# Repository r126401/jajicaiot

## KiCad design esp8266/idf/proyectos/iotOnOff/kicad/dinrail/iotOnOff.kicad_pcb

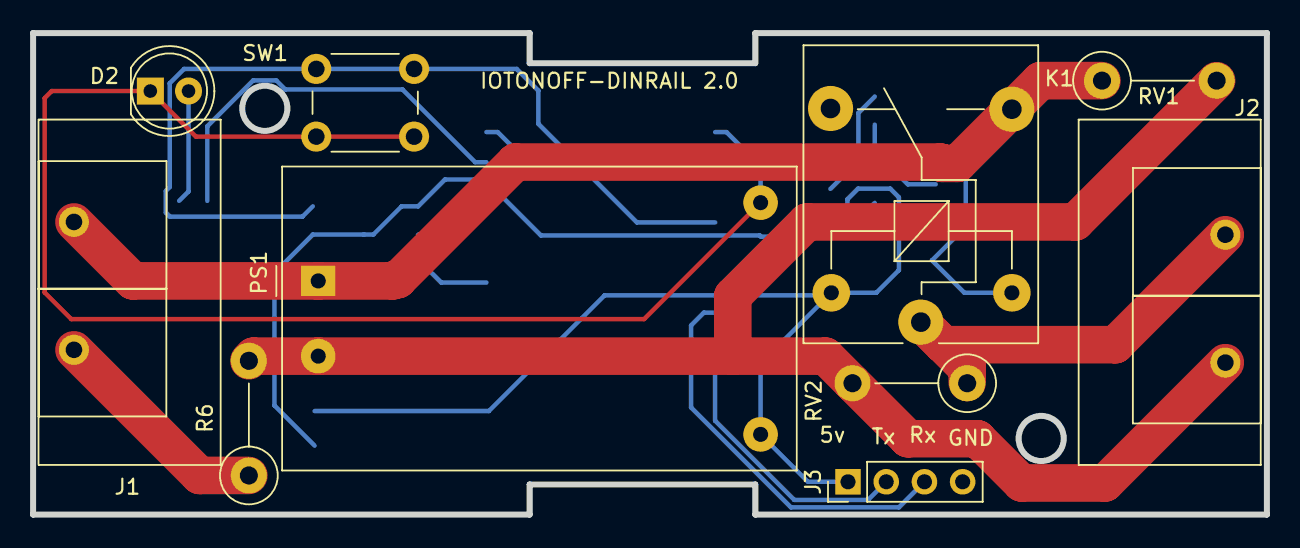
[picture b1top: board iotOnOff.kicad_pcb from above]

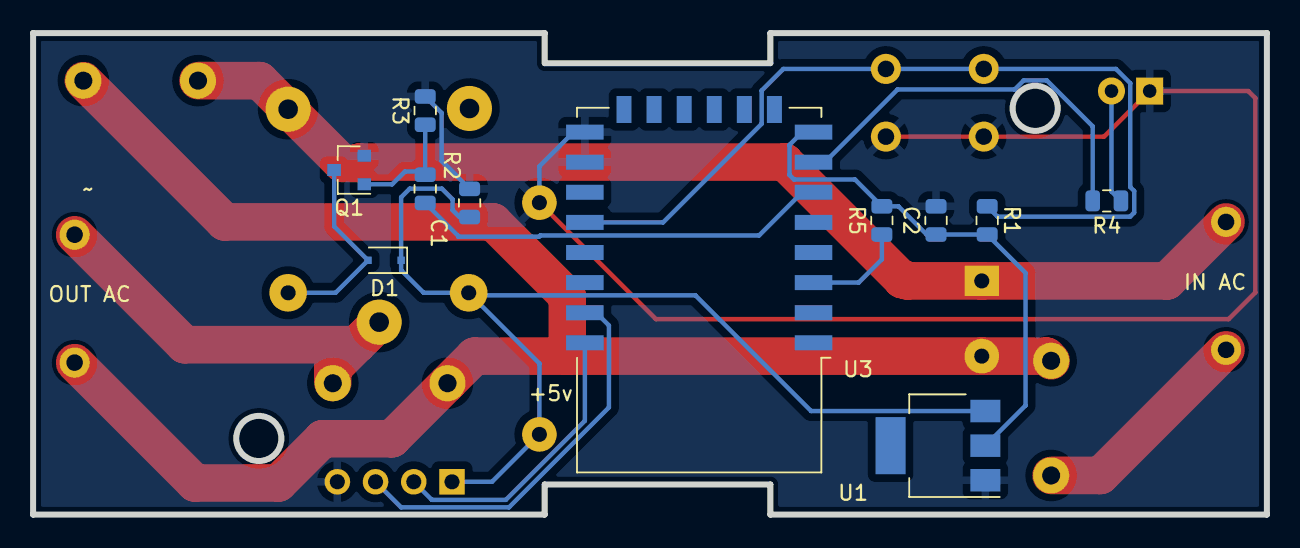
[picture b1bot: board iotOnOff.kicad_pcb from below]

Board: 2 copper layers, 82.0 x 32.0 mm, 21 parts (11 on the bottom side), 16 nets.

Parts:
C1: 10uF; C_0805_2012Metric
C2: 22uF; C_0805_2012Metric
D1: 1N4148; D_SOD-323F
D2: LED; LED_D5.0mm
J1, J2: Conn_01x02; KF8500
J3: Conn_01x04; PinHeader_1x04_P2.54mm_Vertical
K1: SANYOU_SRD_Form_A; Relay_SPDT_SANYOU_SRD_Series_Form_C
PS1: HLK-PM01; Converter_ACDC_HiLink_HLK-PMxx
Q1: 2N7002; SOT-23
R1, R3, R5: 10K; R_0805_2012Metric
R2, R4: 1K; R_0805_2012Metric
R6: 10; R_Axial_DIN0411_L9.9mm_D3.6mm_P7.62mm_Vertical
RV1, RV2: Varistor; R_Axial_DIN0411_L9.9mm_D3.6mm_P7.62mm_Vertical
SW1: SW_Push; SW_PUSH_6mm_H4.3mm
U1: AMS1117-3.3; SOT-223
U3: ESP-12F; ESP-12E

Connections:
GND: C1.2, C2.2, D2.1 (K), J3.4, PS1.3 (-Vout), Q1.2 (S), R3.2, SW1.2, U1.1 (GND), U3.15 (GND), U3.16 (GPIO15)
unnamed: C1.1, D1.1 (K), J3.1, K1.5, PS1.4 (+Vout), U1.3 (VI)
unnamed: C2.1, R1.2, R5.2, U1.2 (VO), U3.8 (VCC)
unnamed: D1.2 (A), K1.2, Q1.3 (D)
unnamed: D2.2 (A), R4.1
unnamed: J1.1, R6.1
unnamed: J1.2, K1.3, PS1.1 (AC/L), RV1.1
unnamed: J2.1, K1.1, RV2.1
unnamed: J2.2, PS1.2 (AC/N), R6.2, RV1.2, RV2.2
unnamed: J3.2, U3.22 (GPIO1/TXD)
unnamed: J3.3, U3.21 (GPIO3/RXD)
unnamed: Q1.1 (G), R2.1, R3.1
unnamed: R1.1, SW1.1, U3.18 (GPIO0)
unnamed: R2.2, U3.6 (GPIO12)
unnamed: R4.2, U3.7 (GPIO13)
unnamed: R5.1, U3.3 (EN)

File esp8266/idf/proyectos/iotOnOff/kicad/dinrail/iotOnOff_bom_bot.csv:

Comment,Designator,Footprint,LCSC Part #
2N7002,Q1,,C179727
10K,R3 R1 R5,,C17414
1K,R2 R4,,C17513
AMS1117-3.3,U1,,C347222
1N4148,D1,, C2128
10uF,C1,,C39060
22uF,C2,,C45783
ESP-12F,U3,,C82891

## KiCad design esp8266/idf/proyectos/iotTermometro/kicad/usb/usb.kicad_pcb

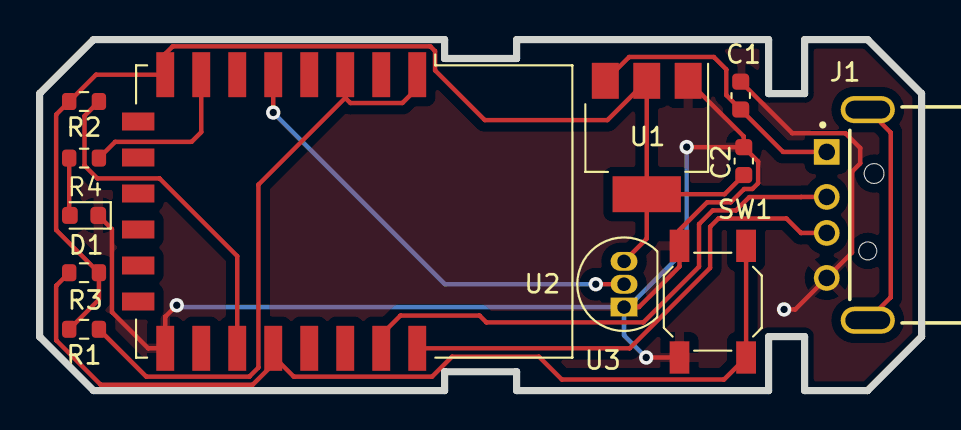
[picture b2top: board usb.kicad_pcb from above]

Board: 2 copper layers, 49.0 x 19.5 mm, 12 parts (0 on the bottom side), 11 nets.

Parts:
C1: 10u; C_0603_1608Metric
C2: 22u; C_0603_1608Metric
D1: LED; LED_0603_1608Metric
J1: USB-AM-S-X-X-TH; SAMTEC_USB-AM-S-X-X-TH
R1, R2: 10k; R_0603_1608Metric
R3, R4: 1K; R_0603_1608Metric
SW1: SW_Push; SW_SPST_SKQG_WithStem
U1: AMS1117-3.3; SOT-223-3_TabPin2
U2: ESP-12F; ESP-12E
U3: DS18B20; TO-92_Inline

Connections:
/LED_FUNCION: R4.1, U2.7 (GPIO13)
/NET_BOTON: R3.2, SW1.1, U2.18 (GPIO0)
/RX: J1.02 (D-), U2.21 (GPIO3/RXD)
/SENSOR_TEMP: U2.5 (GPIO14), U3.2 (DQ)
/TX: J1.03 (D+), U2.22 (GPIO1/TXD)
/VCC: C2.1, R1.2, R2.2, R3.1, U1.2 (VO), U2.8 (VCC), U3.3 (VDD)
/VIN: C1.1, J1.01 (VCC), U1.3 (VI)
GND: C1.2, C2.2, D1.1 (K), J1.04 (GND), SW1.2, U1.1 (GND), U2.15 (GND), U3.1 (GND)
unnamed: D1.2 (A), R4.2
unnamed: R1.1, U2.1 (~RST), U2.3 (EN)
unnamed: R2.1, U2.17 (GPIO2)

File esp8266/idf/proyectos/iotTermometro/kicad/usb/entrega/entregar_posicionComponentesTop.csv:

Ref,Val,Package,Mid X,Mid Y,Rotation,Layer
C1,10u,C_0603_1608Metric,137.950000,-72.360000,90.000000,top
C2,22u,C_0603_1608Metric,138.120000,-76.000000,90.000000,top
D1,LED,LED_0603_1608Metric,101.470000,-79.017000,180.000000,top
J1,USB_A,USB_A_CNCTech_1001-011-01101_Horizontal,150.950000,-78.998500,0.000000,top
R1,10k,R_0603_1608Metric,101.470000,-85.344000,180.000000,top
R2,10k,R_0603_1608Metric,101.470000,-72.690000,180.000000,top
R3,1K,R_0603_1608Metric,101.470000,-82.200500,180.000000,top
R4,1K,R_0603_1608Metric,101.470000,-75.833500,180.000000,top
SW1,SW_Push,SW_SPST_SKQG_WithStem,136.400000,-83.810000,-90.000000,top
U1,AMS1117,SOT-223-3_TabPin2,132.730000,-74.690000,-90.000000,top
U2,ESP-12F,ESP-12E,116.480000,-78.800000,-90.000000,top
U3,S,TO-92_Inline,131.470000,-84.110000,90.000000,top

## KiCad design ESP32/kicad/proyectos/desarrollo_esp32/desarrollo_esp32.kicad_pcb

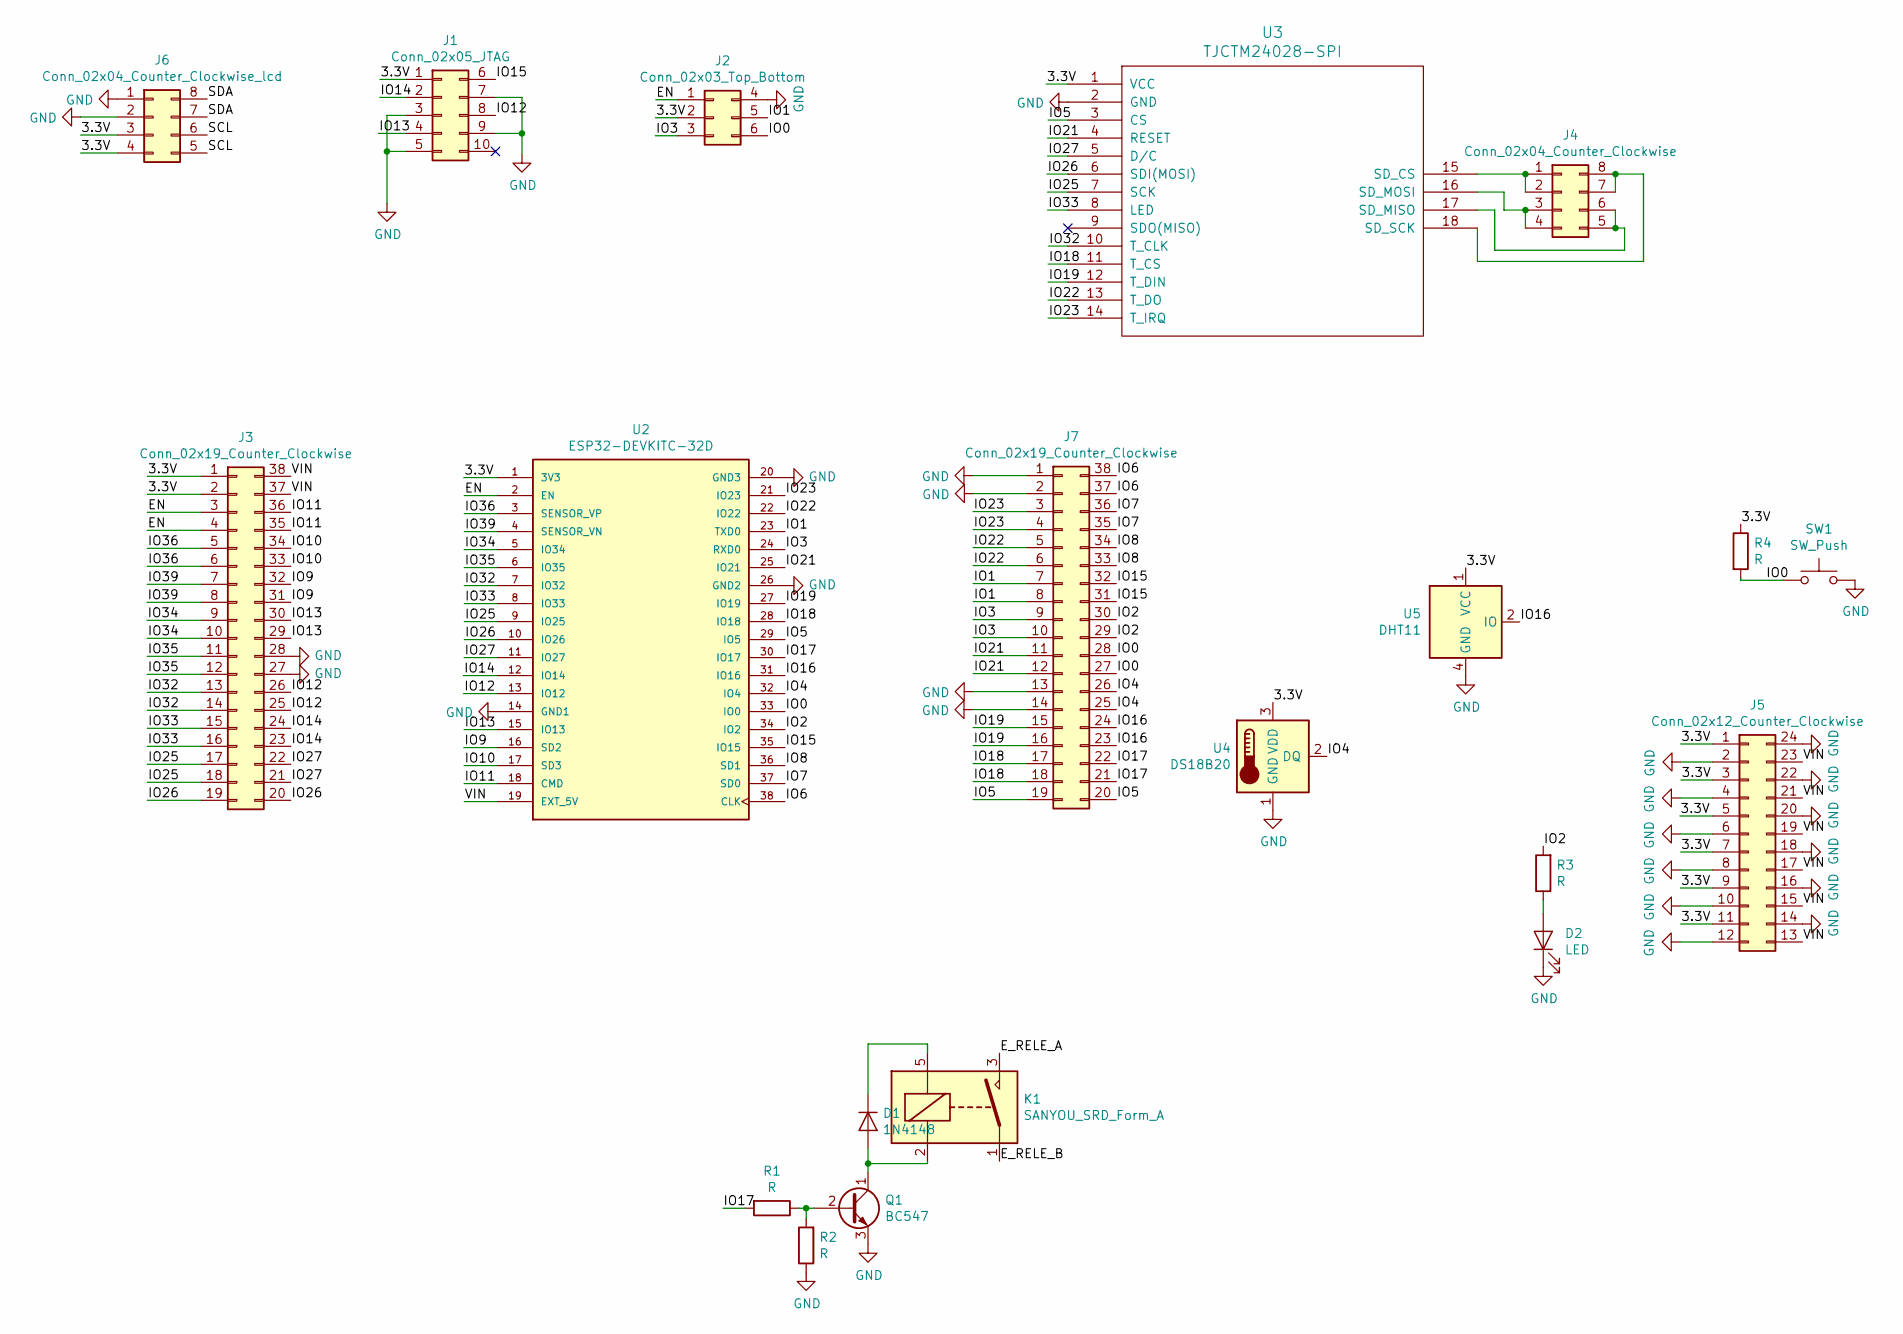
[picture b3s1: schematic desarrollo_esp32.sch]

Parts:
D1: 1N4148; D_DO-34_SOD68_P7.62mm_Horizontal
D2: LED; LED_D5.0mm
J1: Conn_02x05_JTAG; IDC-Header_2x05_P2.54mm_Vertical
J2: Conn_02x03_Top_Bottom; IDC-Header_2x03_P2.54mm_Vertical
J3, J7: Conn_02x19_Counter_Clockwise; PinSocket_2x19_P2.54mm_Vertical
J4: Conn_02x04_Counter_Clockwise; PinSocket_2x04_P2.54mm_Vertical
J5: Conn_02x12_Counter_Clockwise; PinSocket_2x12_P2.54mm_Vertical
J6: Conn_02x04_Counter_Clockwise_lcd; PinSocket_2x04_P2.54mm_Vertical
K1: SANYOU_SRD_Form_A; Relay_SPST_SANYOU_SRD_Series_Form_A
Q1: BC547; TO-92_Inline
R1, R2, R3, R4: R; R_Axial_DIN0207_L6.3mm_D2.5mm_P15.24mm_Horizontal
SW1: SW_Push; SW_PUSH_6mm_H4.3mm
U2: ESP32-DEVKITC-32D; MODULE_ESP32-DEVKITC-32D; PARTREV 4
U3: TJCTM24028-SPI; tjctm24028-spi
U4: DS18B20; TO-92_Inline
U5: DHT11; Aosong_DHT11_5.5x12.0_P2.54mm

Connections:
/3.3V: J1.1, J2.2, J3.1, J3.2, J5.1, J5.3, J5.5, J5.7, J5.9, J5.11, J6.3, J6.4, R4.1, U2.1 (3V3), U3.1 (VCC), U4.3 (VDD), U5.1 (VCC)
/EN: J2.1, J3.3, J3.4, U2.2 (EN)
/E_RELE_A: K1.3
/E_RELE_B: K1.1
/IO0: J2.6, J7.27, J7.28, R4.2, SW1.1, U2.33 (IO0)
/IO1: J2.5, J7.7, J7.8, U2.23 (TXD0)
/IO2: J7.29, J7.30, R3.2, U2.34 (IO2)
/IO3: J2.3, J7.9, J7.10, U2.24 (RXD0)
/IO4: J7.25, J7.26, U2.32 (IO4), U4.2 (DQ)
/IO5: J7.19, J7.20, U2.29 (IO5), U3.3 (CS)
/IO6: J7.37, J7.38, U2.38 (CLK)
/IO7: J7.35, J7.36, U2.37 (SD0)
/IO8: J7.33, J7.34, U2.36 (SD1)
/IO9: J3.31, J3.32, U2.16 (SD2)
/IO10: J3.33, J3.34, U2.17 (SD3)
/IO11: J3.35, J3.36, U2.18 (CMD)
/IO12: J1.8, J3.25, J3.26, U2.13 (IO12)
/IO13: J1.4, J3.29, J3.30, U2.15 (IO13)
/IO14: J1.2, J3.23, J3.24, U2.12 (IO14)
/IO15: J1.6, J7.31, J7.32, U2.35 (IO15)
/IO16: J7.23, J7.24, U2.31 (IO16), U5.2 (IO)
/IO17: J7.21, J7.22, R1.2, U2.30 (IO17)
/IO18: J7.17, J7.18, U2.28 (IO18), U3.11 (T_CS)
/IO19: J7.15, J7.16, U2.27 (IO19), U3.12 (T_DIN)
/IO21: J7.11, J7.12, U2.25 (IO21), U3.4 (RESET)
/IO22: J7.5, J7.6, U2.22 (IO22), U3.13 (T_DO)
/IO23: J7.3, J7.4, U2.21 (IO23), U3.14 (T_IRQ)
/IO25: J3.17, J3.18, U2.9 (IO25), U3.7 (SCK)
/IO26: J3.19, J3.20, U2.10 (IO26), U3.6 (SDI(MOSI))
/IO27: J3.21, J3.22, U2.11 (IO27), U3.5 (D/C)
/IO32: J3.13, J3.14, U2.7 (IO32), U3.10 (T_CLK)
/IO33: J3.15, J3.16, U2.8 (IO33), U3.8 (LED)
/IO34: J3.9, J3.10, U2.5 (IO34)
/IO35: J3.11, J3.12, U2.6 (IO35)
/IO36: J3.5, J3.6, U2.3 (SENSOR_VP)
/IO39: J3.7, J3.8, U2.4 (SENSOR_VN)
/SCL: J6.5, J6.6
/SDA: J6.7, J6.8
/VIN: J3.37, J3.38, J5.13, J5.15, J5.17, J5.19, J5.21, J5.23, U2.19 (EXT_5V)
GND: D2.1 (K), J1.3, J1.5, J1.7, J1.9, J2.4, J3.27, J3.28, J5.2, J5.4, J5.6, J5.8, J5.10, J5.12, J5.14, J5.16, J5.18, J5.20, J5.22, J5.24, J6.1, J6.2, J7.1, J7.2, J7.13, J7.14, Q1.3 (E), R2.1, SW1.2, U2.14 (GND1), U2.20 (GND3), U2.26 (GND2), U3.2 (GND), U4.1 (GND), U5.4 (GND)
unnamed: D1.1 (K), K1.5
unnamed: D1.2 (A), K1.2, Q1.1 (C)
unnamed: D2.2 (A), R3.1
unnamed: J4.1, J4.2, U3.15 (SD_CS)
unnamed: J4.3, J4.4, U3.16 (SD_MOSI)
unnamed: J4.5, J4.6, U3.17 (SD_MISO)
unnamed: J4.7, J4.8, U3.18 (SD_SCK)
unnamed: Q1.2 (B), R1.1, R2.2

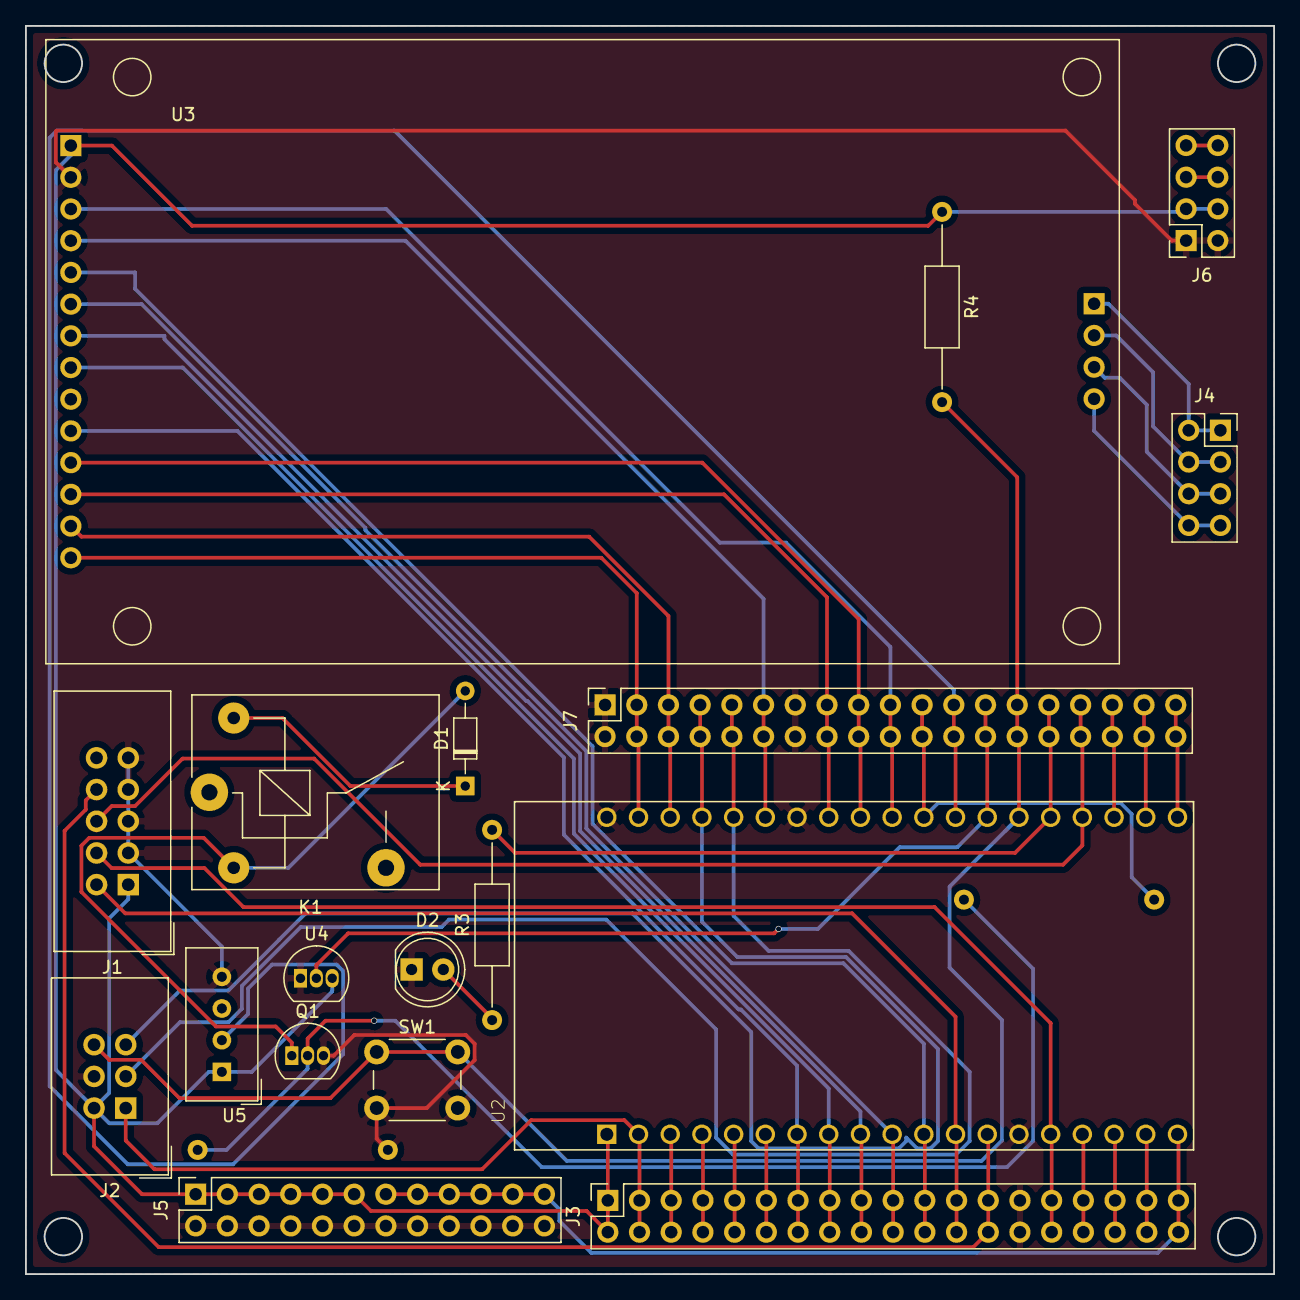
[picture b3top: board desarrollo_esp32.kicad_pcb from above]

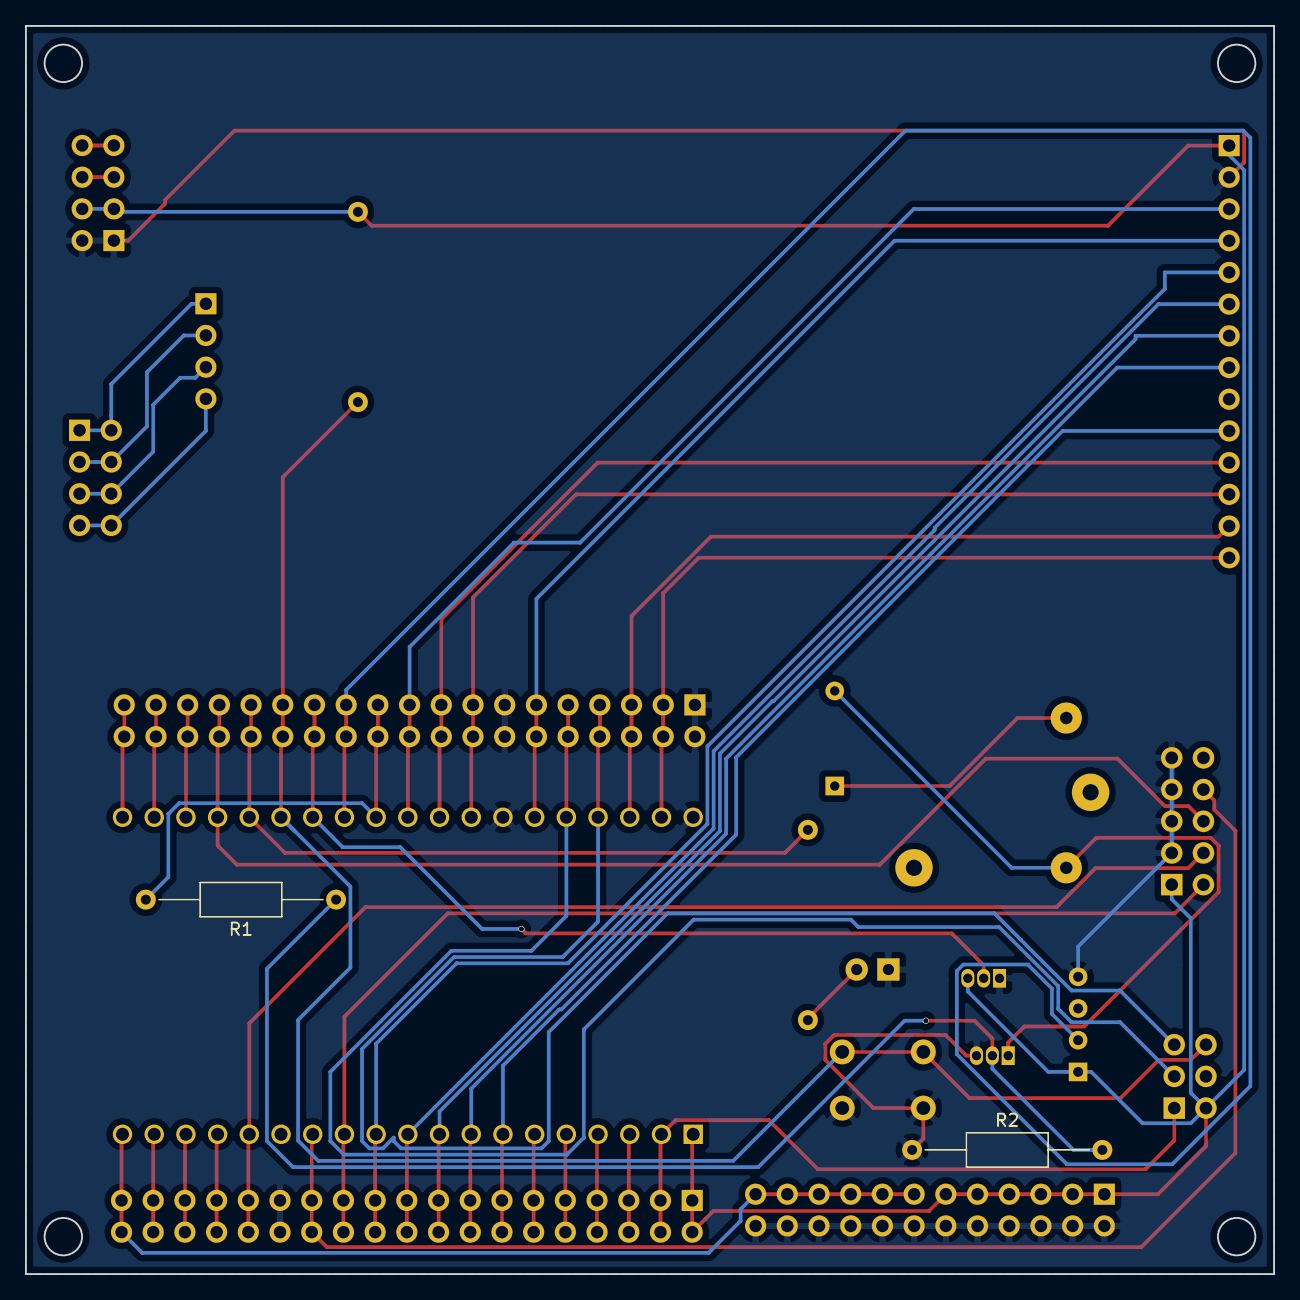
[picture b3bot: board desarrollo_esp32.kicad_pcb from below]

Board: 2 copper layers, 100.0 x 100.0 mm, 20 parts (2 on the bottom side), 46 nets.

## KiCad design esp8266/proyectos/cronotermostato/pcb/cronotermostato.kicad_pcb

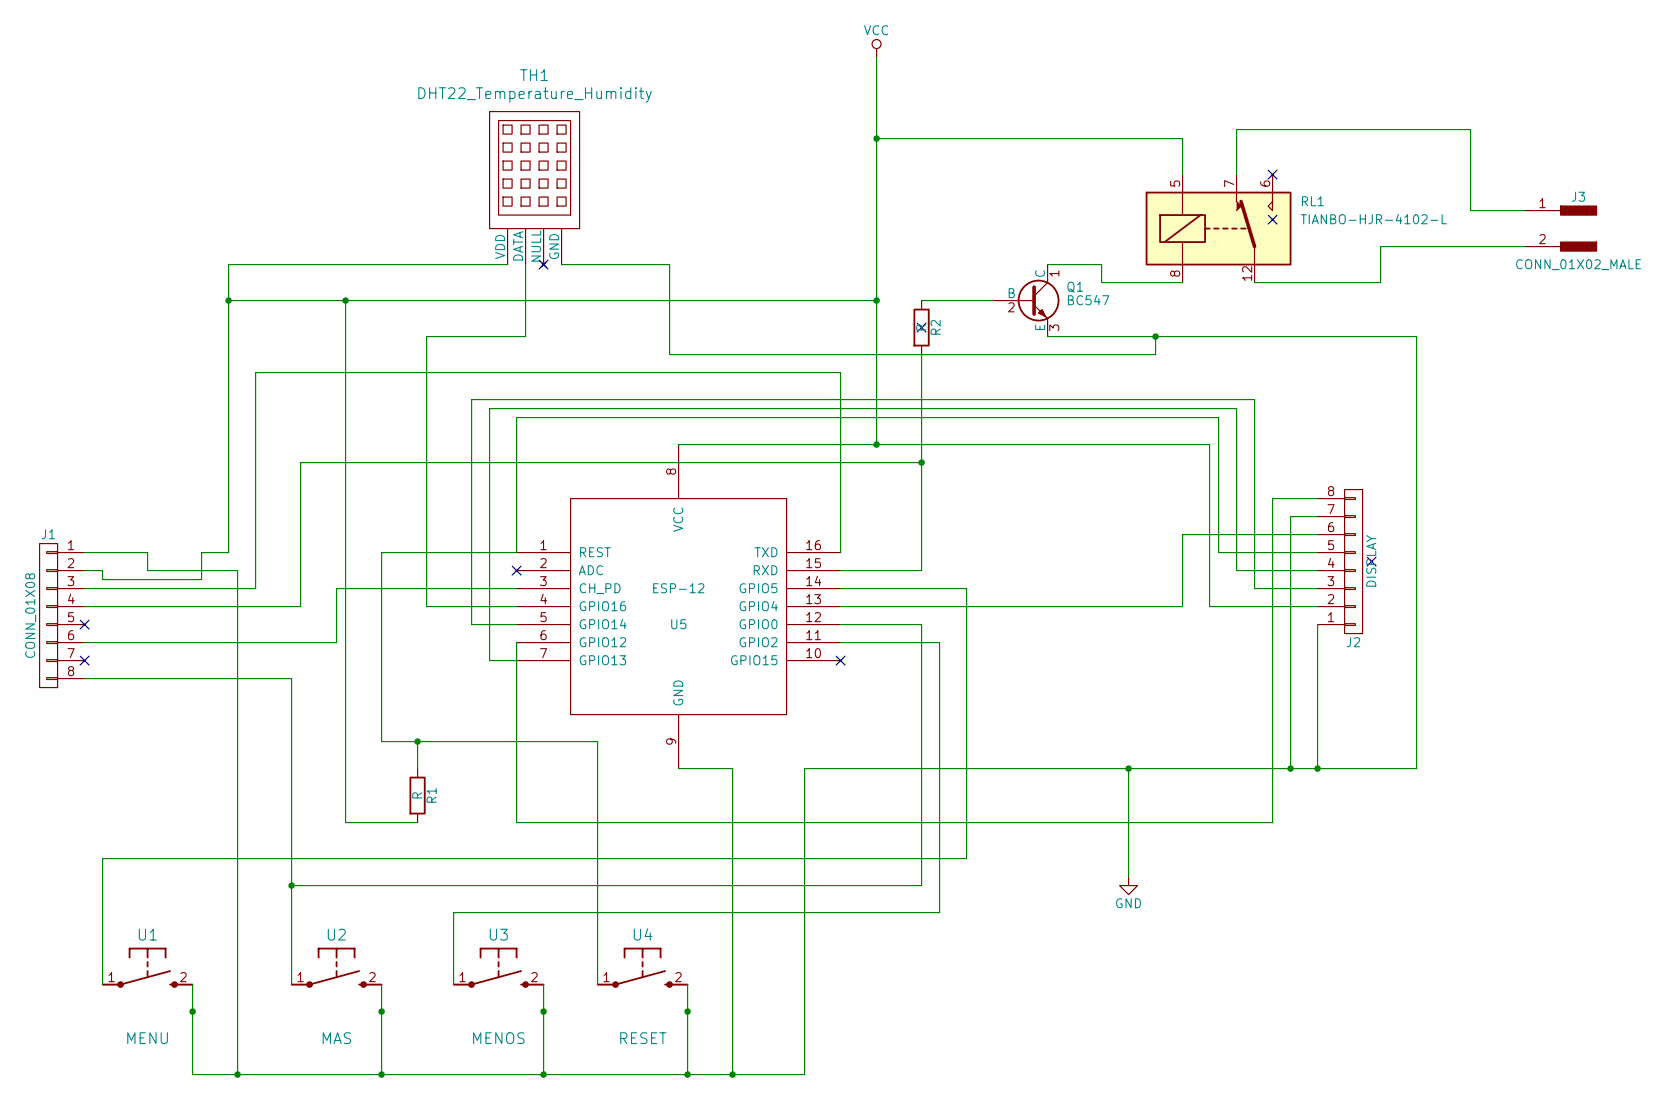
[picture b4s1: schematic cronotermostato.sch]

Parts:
J1: CONN_01X08; JST_EH_B08B-EH-A_08x2.50mm_Straight
J2: DISPLAY; JST_EH_B08B-EH-A_08x2.50mm_Straight
J3: CONN_01X02_MALE; JST_EH_B02B-EH-A_02x2.50mm_Straight
Q1: BC547; TO-92_Molded_Narrow
R1, R2: R; R_Axial_DIN0207_L6.3mm_D2.5mm_P7.62mm_Horizontal
RL1: TIANBO-HJR-4102-L; Relay_SPDT_HJR-4102
TH1: DHT22_Temperature_Humidity; JST_EH_B04B-EH-A_04x2.50mm_Straight
U1: MENU; SW_SPST_EVQP0
U2: MAS; SW_SPST_EVQP0
U3: MENOS; SW_SPST_EVQP0
U4: RESET; SW_SPST_EVQP0
U5: ESP-12; ESP-12E

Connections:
GND: J1.1, J2.1, J2.7, Q1.3 (E), TH1.4 (GND), U1.2, U2.2, U3.2, U4.2, U5.9 (GND)
unnamed: J1.3, U5.16 (TXD)
unnamed: J1.4, R2.2, U5.15 (RXD)
unnamed: J1.6, U5.3 (CH_PD)
unnamed: J1.8, U2.1, U5.12 (GPIO0)
unnamed: J2.3, U5.5 (GPIO14)
unnamed: J2.4, U5.7 (GPIO13)
unnamed: J2.5, R1.1, U4.1, U5.1 (REST)
unnamed: J2.6, U5.13 (GPIO4)
unnamed: J2.8, U5.6 (GPIO12)
unnamed: J3.1, RL1.7
unnamed: J3.2, RL1.12
unnamed: Q1.1 (C), RL1.8
unnamed: Q1.2 (B), R2.1
unnamed: TH1.2 (DATA), U5.4 (GPIO16)
unnamed: U1.1, U5.14 (GPIO5)
unnamed: U3.1, U5.11 (GPIO2)
VCC: J1.2, J2.2, R1.2, RL1.5, TH1.1 (VDD), U5.8 (VCC)

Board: 2 copper layers, 13 parts (0 on the bottom side), 18 nets, no tracks yet.

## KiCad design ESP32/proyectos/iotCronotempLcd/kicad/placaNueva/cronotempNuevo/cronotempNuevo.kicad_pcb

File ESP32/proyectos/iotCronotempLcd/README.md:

# iotOnOff

IotOnff es una aplicacion para controlar dispositivos interruptores.

python instalar.py jajicaiot.ddns.net 1883 /mnt/servidorWeb /mnt/servidorWeb iotCronotempLcd 2006161948 /mnt/servidorWeb jajicaiot.ddns.net/firmware/iotCronoTemp/

instalar.py es un script que genera el fichero lastVersion en el que se indican los datos de la ultima version compilada para el posterior upgrade ota desde el dispositivo. Por tanto, es necesario aportar al script la siguiente informacion.

Servidor mqtt: jajicaiot.ddns.net
Puerto mqtt: 1883
directorio de instalacion: /mnt/servidorWeb es el directorio base del servidor que recibira las peticiones ota
directorio imagen: servidorWeb es el directorio donde se alamacenara el binario recien compilado.
nombre_proyecto: Se utiliza para meter dentro del directorio dentro del dispositivo la imagen
version_ota: Es la version del dispositivo
directorio lastVersion

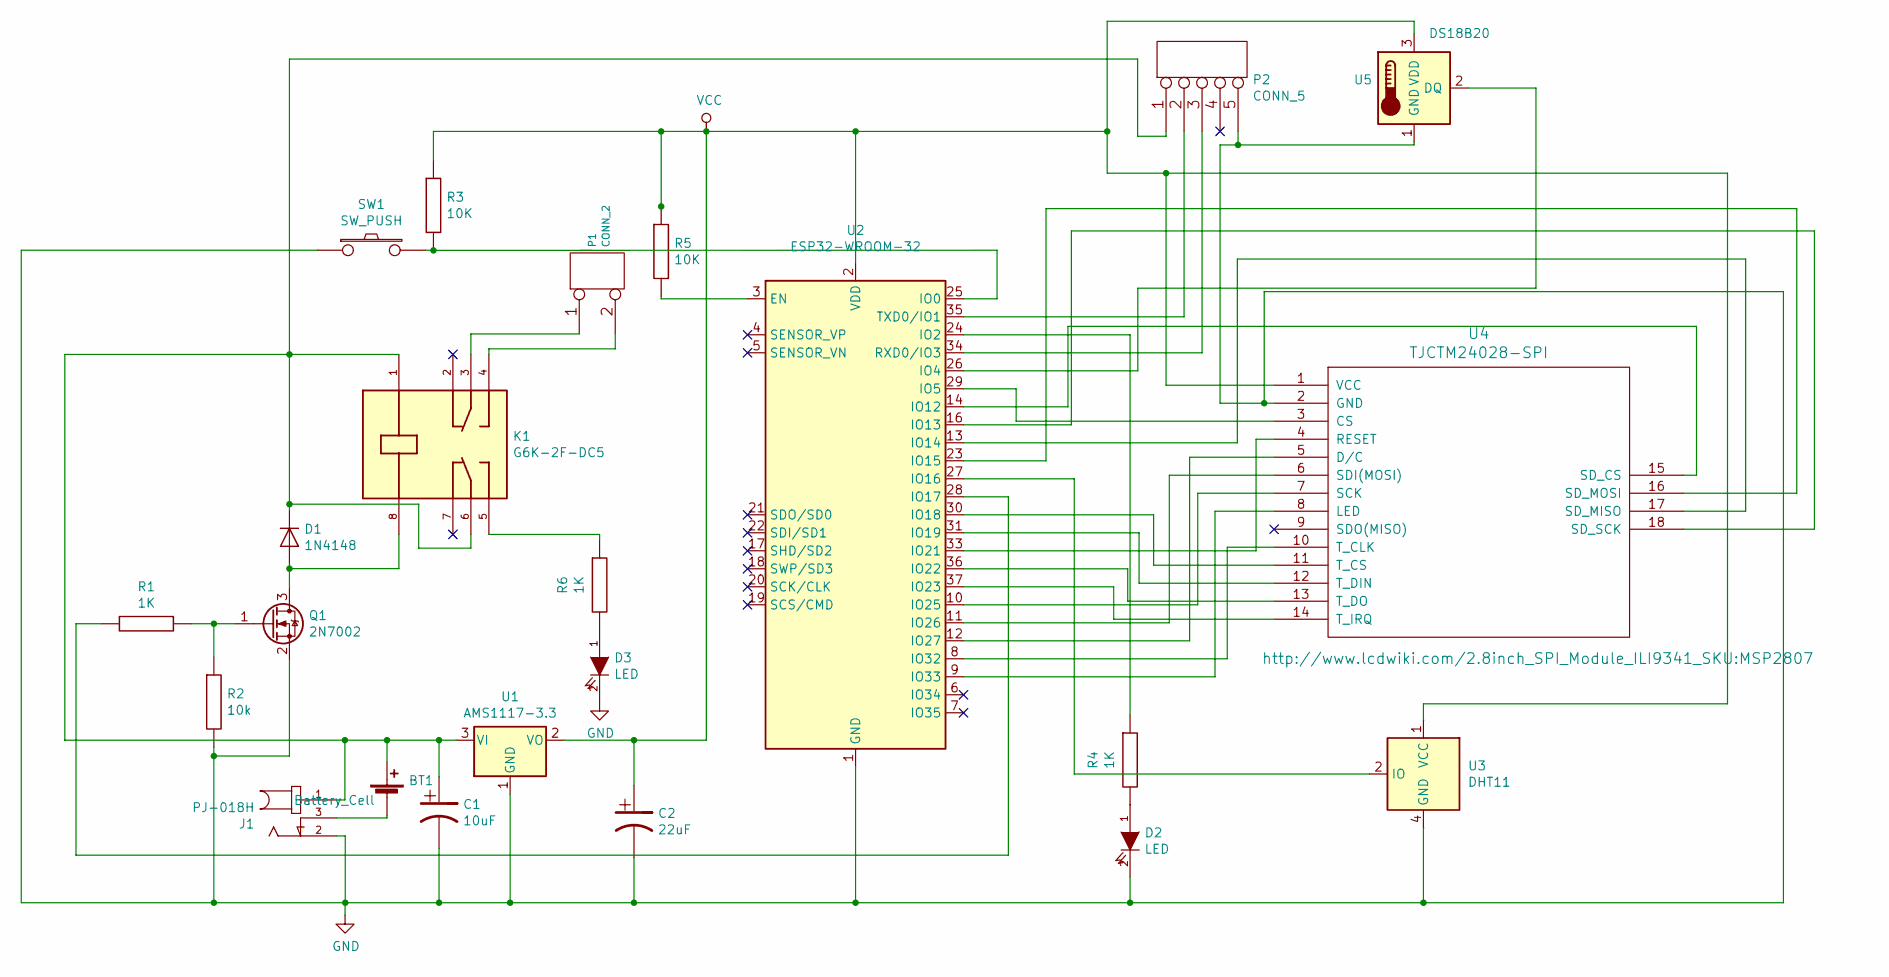
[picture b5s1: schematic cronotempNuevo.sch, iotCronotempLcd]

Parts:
BT1: Battery_Cell; SolderWirePad_1x02_P5.08mm_Drill1.5mm
C1: 10uF; C_0805_2012Metric
C2: 22uF; C_0805_2012Metric
D1: 1N4148; D_SOD-323F
D2, D3: LED; LED_D5.0mm
J1: PJ-018H; CUI_PJ-018H
K1: G6K-2F-DC5; RELAY_G6K-2F-DC5
P1: CONN_2; TerminalBlock_Phoenix_MKDS-1,5-2-5.08_1x02_P5.08mm_Horizont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
P2: CONN_5; PinHeader_1x05_P2.54mm_Vertical
Q1: 2N7002; SOT-23
R1, R4, R6: 1K; R_0805_2012Metric
R2: 10k; R_0805_2012Metric
R3, R5: 10K; R_0805_2012Metric
SW1: SW_PUSH; SW_PUSH_6mm_H4.3mm
U1: AMS1117-3.3; SOT-223
U2: ESP32-WROOM-32
U3: DHT11; Aosong_DHT11_5.5x12.0_P2.54mm
U4: TJCTM24028-SPI; msp3218
U5: DS18B20; TO-92L_Inline

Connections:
GND: C1.2, C2.2, D2.2 (K), D3.2 (K), J1.2, P2.5, Q1.2 (S), R2.2, SW1.1, U1.1 (GND), U2.1 (GND), U2.15 (GND), U2.38 (GND), U2.39 (GND), U3.4 (GND), U4.2 (GND), U5.1 (GND)
unnamed: BT1.1 (+), C1.1, D1.1 (K), J1.1, K1.1, K1.6, P2.1, U1.3 (VI)
unnamed: BT1.2 (-), J1.3
unnamed: D1.2 (A), K1.8, Q1.3 (D)
unnamed: D2.1 (A), R4.2
unnamed: D3.1 (A), R6.2
unnamed: K1.3, P1.1
unnamed: K1.4, P1.2 (PM)
unnamed: K1.5, R6.1
unnamed: P2.2, U2.35 (TXD0/IO1)
unnamed: P2.3, U2.34 (RXD0/IO3)
unnamed: Q1.1 (G), R1.1, R2.1
unnamed: R1.2, U2.28 (IO17)
unnamed: R3.2, SW1.2, U2.25 (IO0)
unnamed: R4.1, U2.24 (IO2)
unnamed: R5.2, U2.3 (EN)
unnamed: U2.8 (IO32), U4.10 (T_CLK)
unnamed: U2.9 (IO33), U4.8 (LED)
unnamed: U2.10 (IO25), U4.7 (SCK)
unnamed: U2.11 (IO26), U4.6 (SDI(MOSI))
unnamed: U2.12 (IO27), U4.5 (D/C)
unnamed: U2.13 (IO14), U4.17 (SD_MISO)
unnamed: U2.14 (IO12), U4.15 (SD_CS)
unnamed: U2.16 (IO13), U4.18 (SD_SCK)
unnamed: U2.23 (IO15), U4.16 (SD_MOSI)
unnamed: U2.26 (IO4), U5.2 (DQ)
unnamed: U2.27 (IO16), U3.2 (IO)
unnamed: U2.29 (IO5), U4.3 (CS)
unnamed: U2.30 (IO18), U4.11 (T_CS)
unnamed: U2.31 (IO19), U4.12 (T_DIN)
unnamed: U2.33 (IO21), U4.4 (RESET)
unnamed: U2.36 (IO22), U4.13 (T_DO)
unnamed: U2.37 (IO23), U4.14 (T_IRQ)
VCC: C2.1, R3.1, R5.1, U1.2 (VO), U2.2 (VDD), U3.1 (VCC), U4.1 (VCC), U5.3 (VDD)

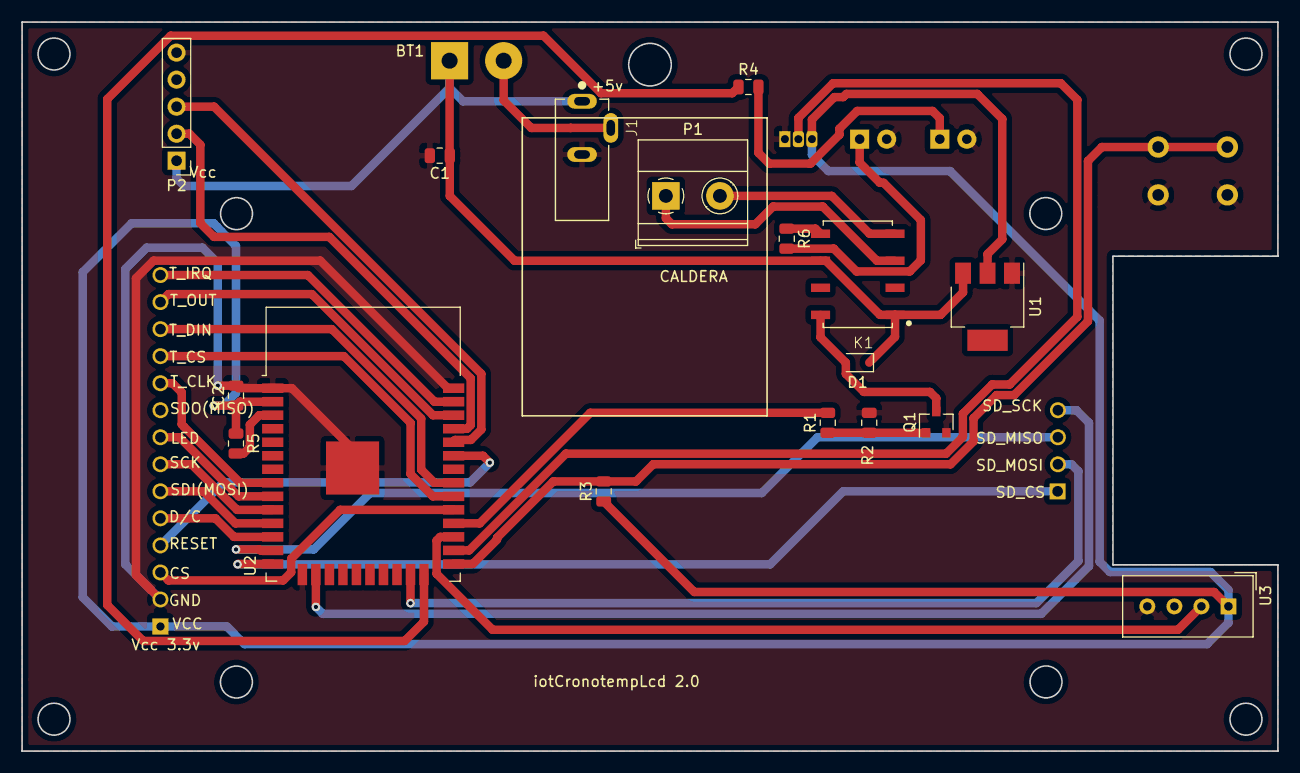
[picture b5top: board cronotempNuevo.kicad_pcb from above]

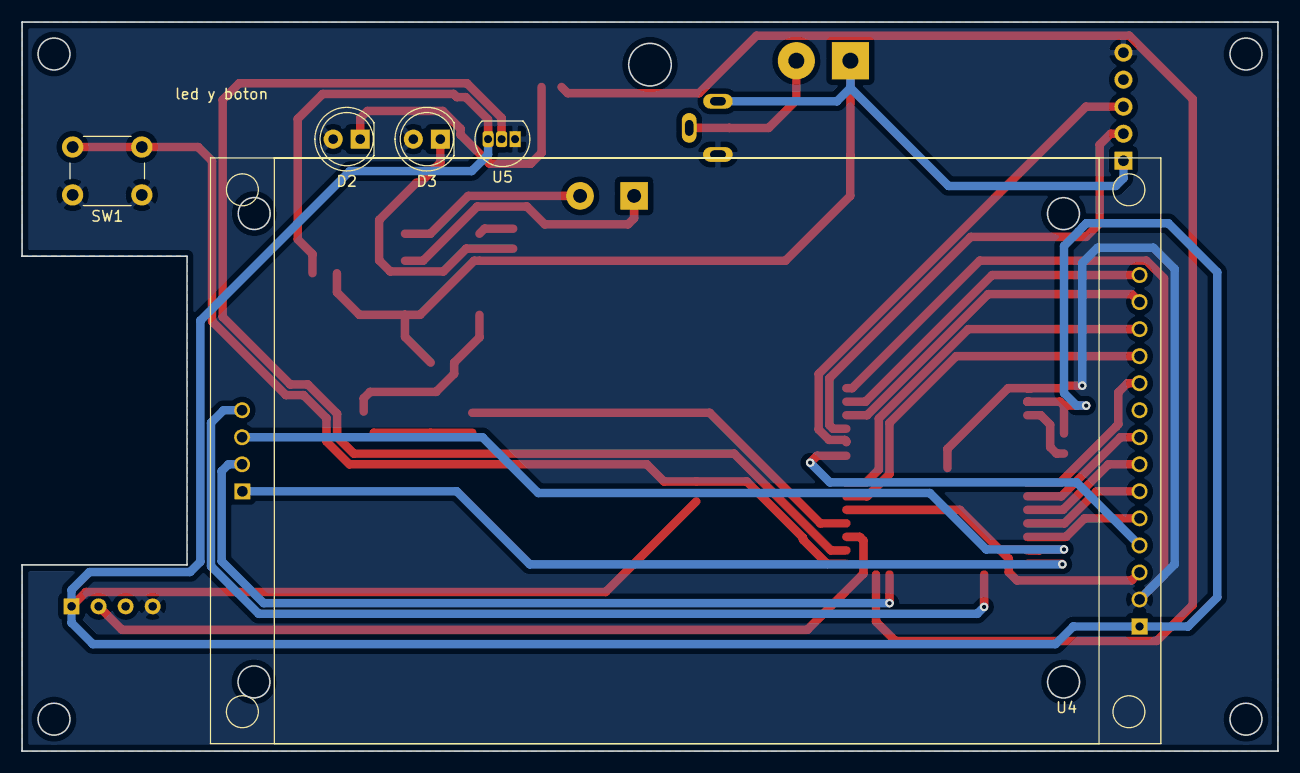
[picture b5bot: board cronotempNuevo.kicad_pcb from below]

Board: 2 copper layers, 118.0 x 68.5 mm, 23 parts (5 on the bottom side), 34 nets.

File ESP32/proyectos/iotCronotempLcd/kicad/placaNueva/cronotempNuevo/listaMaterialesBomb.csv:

Comment,Designator,Footprint,LCSC
Battery_Cell,BT1,Connector_Wire:SolderWirePad_1x02_P5.08mm_Drill1.5mm,
10uF,C1,Capacitor_SMD:C_0805_2012Metric,C39060
22uF,C2,Capacitor_SMD:C_0805_2012Metric,C45783
1N4148,D1,Diode_THT:D_DO-35_SOD27_P7.62mm_Horizontal, C2128
LED,D2,LED_THT:LED_D5.0mm,
PJ-018H,J1,jack4_8mm:CUI_PJ-018H,
G6K-2F-DC5,K1,releOmron:RELAY_G6K-2F-DC5,C397196
CONN_2,P1,"TerminalBlock_Phoenix:TerminalBlock_Phoenix_MKDS-1,5-2-5.08_1x02_P5.08mm_Horizontal",
CONN_4,P2,Connector_PinHeader_2.54mm:PinHeader_1x04_P2.54mm_Vertical,
2N7002,Q1,Package_TO_SOT_SMD:SOT-23,C179727
10k,R2,Resistor_SMD:R_0805_2012Metric,C17414
1K,"R1,R3,R4",Resistor_SMD:R_0805_2012Metric,C17513
SW_PUSH,SW1,Button_Switch_THT:SW_PUSH_6mm_H4.3mm,
AMS1117-3.3,U1,Package_TO_SOT_SMD:SOT-223-3_TabPin2,C347222
ESP32-WROOM-32D,U2,RF_Module:ESP32-WROOM-32,C473012
DHT11,U3,Sensor:Aosong_DHT11_5.5x12.0_P2.54mm,
TJCTM24028-SPI,U4,iotCronotempLcd:tjctm24028-spi,
DS18B20,U5,Package_TO_SOT_THT:TO-92L_Inline,

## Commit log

2021-11-26 primera importacion
2021-12-02 gitignore
2021-12-02 vacio
2021-12-02 Eliminamos la version antigua de iotTermostato
2021-12-02 eliminamos iotTermometro antiguo
2021-12-02 importacion inicial de iotTermometro
2021-12-02 # WARNING: head commit changed in the meantime
    Se incorporan al proyecto los ficheros de certificados
2021-12-02 importacion del componente dht22
2021-12-02 # WARNING: head commit changed in the meantime
    a
2021-12-03 sdkconfig
2021-12-03 Se hace que el led se encienda o apague segun este el rele encendido o no.
2021-12-10 lo dejamos como estaba
2021-12-16 se elimina el rebote del boton por encendido de la luz
2021-12-17 Se incluye el certificado en la libreria para conectar todos los dispositivos por tls
2021-12-17 Se introduce el codigo para que todos los dispositivos se conecten al broker por conexion segura tls
2021-12-17 se introduce la logica para conectar los dispositivos por tls
2021-12-17 kicad para iotOnoff dinrail
2021-12-17 movimiento de archivos
2021-12-17 Se añade la inclusion del certificado en la libreria para los proyectos de ESP32 con CMAKE
2021-12-17 Se inserta el certificado dentro de la libreria de ota
2021-12-17 Se incluye el certificado dentro de la libreria espota
2021-12-17 Se mete el certificado dentro de la libreria espota
2021-12-17 se borra lo sobrante
2021-12-17 se borra porque ya se incrusta en espota
2022-01-04 modulos actualizados para ota y mqtt sobre SSL
2022-01-04 se implementa OTA over SSL con mqtt over SSL
2022-01-04 espota
2022-01-04 se implementa upgrade ssl para esp8266
2022-01-04 se quita el keep alive
2022-01-04 se añade el fichero de secuencia de estados
2022-01-05 se añade como un componente mas
2022-01-05 se pone skip
2022-01-07 funciona lo principal del termometro
2022-01-07 Se tiene una primera version con sensor de temperatura ds18b20 funcionando
2022-01-07 se añaden las librerias de ds18b20 a componentes
2022-01-07 Se añaden las funciones para visualizar y modificar los parametros de la aplicacion
2022-01-15 se recuperan los valores para el lcd y el touch panel
2022-01-19 construccion del proyecto
2022-01-28 Se añade el proyecto pcb de iot Termometro usb para la aplicacion easyeda
2022-04-29 Se mete el redondeo en la medida de la temperatura
2022-05-17 Se modifica accion_Temporizada para meter appuser_cambiar_modo_aplicacion(datosApp, NORMAL_AUTO);
2022-05-17 Ahora si que se pone bien el estado FIN_PROGRAMA_ACTIVO en la funcion appuser_ejecucion_accion_temporizada
2022-06-15 Se introduce el fin de upgrade en le arranque de aplicacion.
2022-06-16 Se crea el escenario ota para esp8266
2022-06-17 Se implementa correctamente el escenario ota con la aplicacion movil
2022-06-18 Se cambia la ruta de instalacion en el Makefile
2022-06-24 Se corrige la conexion de GPIO15 en dinrail
2022-06-25 Se corrigen problemas cuando no hay programacion
2022-09-26 Se quitan los programas de interfaz de usuario por defecto.
2023-05-17 se añade el estado del rele cuando se cambia el umbral de temperatura
2023-05-22 avanzamos
2023-05-24 Se soluciona el problema de asignacion del sensor para el cronotermostato
2023-06-02 Se deja en version definitiva linkada a espressif 4.4.2
2023-09-04 fdasfd
